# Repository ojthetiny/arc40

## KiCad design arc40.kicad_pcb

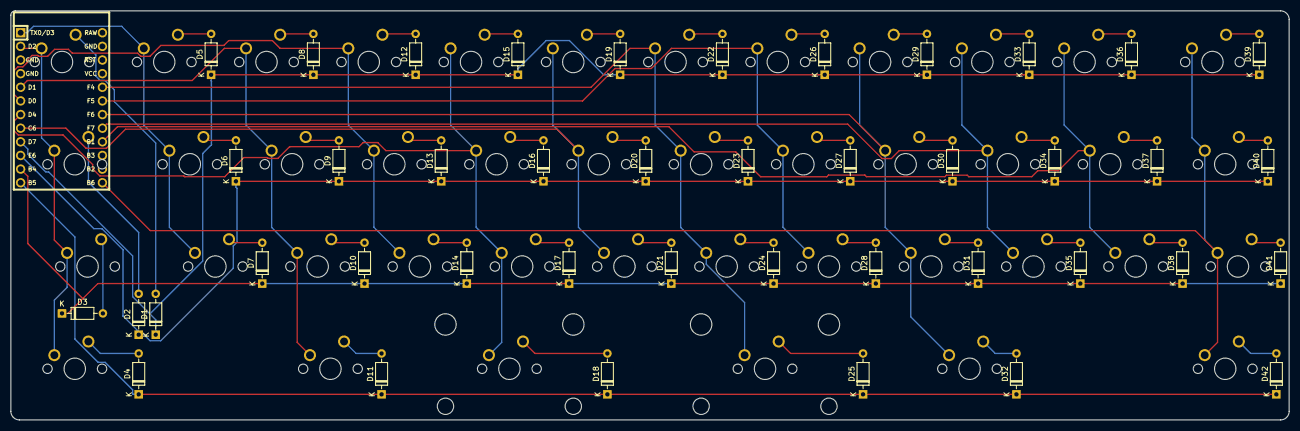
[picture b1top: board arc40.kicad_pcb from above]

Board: 2 copper layers, 238.1 x 76.2 mm, 85 parts (0 on the bottom side), 58 nets.

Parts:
D1, D2, D3, D4, D5, D6, D7, D8, D9, D10, D11, D12, D13, D14, D15, D16, D17, D18, D19, D20, D21, D22, D23, D24, D25, D26, D27, D28, D29, D30, D31, D32, D33, D34, D35, D36, D37, D38, D39, D40, D41, D42: D_Small; D_DO-35_SOD27_P7.62mm_Horizontal
MX1, MX5, MX6, MX7, MX8, MX9, MX10, MX12, MX13, MX14, MX15, MX16, MX17, MX19, MX20, MX21, MX22, MX23, MX24, MX26, MX27, MX28, MX29, MX30, MX31, MX33, MX34, MX35, MX36, MX37, MX38, MX41: MX-NoLED; MXOnly-1U-NoLED
MX2, MX4, MX11, MX32, MX40, MX42: MX-NoLED; MXOnly-1.25U-NoLED
MX3, MX39: MX-NoLED; MXOnly-1.5U-NoLED
MX18: MX-NoLED; MXOnly-2.25U-ReversedStabilizers-NoLED
MX25: MX-NoLED; MXOnly-2.75U-ReversedStabilizers-NoLED
U1: ProMicro; ArduinoProMicro

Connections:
COL0: MX1.1, MX2.1, MX3.1, MX4.1, U1.2
COL1: MX5.1, MX6.1, MX7.1, U1.1
COL2: MX8.1, MX9.1, MX10.1, MX11.1, U1.5
COL3: MX12.1, MX13.1, MX14.1, U1.6
COL4: MX15.1, MX16.1, MX17.1, MX18.1, U1.7
COL5: MX19.1, MX20.1, MX21.1, U1.8
COL6: MX22.1, MX23.1, MX24.1, MX25.1, U1.20
COL7: MX26.1, MX27.1, MX28.1, U1.19
COL8: MX29.1, MX30.1, MX31.1, MX32.1, U1.18
COL9: MX33.1, MX34.1, MX35.1, U1.17
COL10: MX36.1, MX37.1, MX38.1, U1.16
COL11: MX39.1, MX40.1, MX41.1, MX42.1, U1.13
unnamed: D1.2, MX1.2
unnamed: D2.2, MX2.2
unnamed: D3.2, MX3.2
unnamed: D4.2, MX4.2
unnamed: D5.2, MX5.2
unnamed: D6.2, MX6.2
unnamed: D7.2, MX7.2
unnamed: D8.2, MX8.2
unnamed: D9.2, MX9.2
unnamed: D10.2, MX10.2
unnamed: D11.2, MX11.2
unnamed: D12.2, MX12.2
unnamed: D13.2, MX13.2
unnamed: D14.2, MX14.2
unnamed: D15.2, MX15.2
unnamed: D16.2, MX16.2
unnamed: D17.2, MX17.2
unnamed: D18.2, MX18.2
unnamed: D19.2, MX19.2
unnamed: D20.2, MX20.2
unnamed: D21.2, MX21.2
unnamed: D22.2, MX22.2
unnamed: D23.2, MX23.2
unnamed: D24.2, MX24.2
unnamed: D25.2, MX25.2
unnamed: D26.2, MX26.2
unnamed: D27.2, MX27.2
unnamed: D28.2, MX28.2
unnamed: D29.2, MX29.2
unnamed: D30.2, MX30.2
unnamed: D31.2, MX31.2
unnamed: D32.2, MX32.2
unnamed: D33.2, MX33.2
unnamed: D34.2, MX34.2
unnamed: D35.2, MX35.2
unnamed: D36.2, MX36.2
unnamed: D37.2, MX37.2
unnamed: D38.2, MX38.2
unnamed: D39.2, MX39.2
unnamed: D40.2, MX40.2
unnamed: D41.2, MX41.2
unnamed: D42.2, MX42.2
ROW0: D1.1, D5.1, D8.1, D12.1, D15.1, D19.1, D22.1, D26.1, D29.1, D33.1, D36.1, D39.1, U1.9
ROW1: D2.1, D6.1, D9.1, D13.1, D16.1, D20.1, D23.1, D27.1, D30.1, D34.1, D37.1, D40.1, U1.10
ROW2: D3.1, D7.1, D10.1, D14.1, D17.1, D21.1, D24.1, D28.1, D31.1, D35.1, D38.1, D41.1, U1.11
ROW3: D4.1, D11.1, D18.1, D25.1, D32.1, D42.1, U1.12

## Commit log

2021-02-03 add gerbers
2021-02-13 added a small little detail called board edges
